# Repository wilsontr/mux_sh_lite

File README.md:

# mux_sh lite
This is a simplified version of the mux_sh accent mod board for the e-licktronic Nava TR-909 clone. It eliminates three of the sample & hold circuits attached to the multiplexer, because these circuits are unconnected to any part of the Nava accent circuitry. 

## Rationale
I had trouble getting the mux_sh boards included with my Nava to work correctly. Even after much tinkering and testing, I'd get erratic or unpredictable accent behavior from them. I'd get completely different behavior after reflowing any given solder joint on the board.  

I decided to try getting rid of the unused S&H circuits, thereby removing three opamps, several capacitors, and many traces and vias from the PCB design. So far, with the reduced density on the very small PCB, things seem to be more stable and reliable. 

[e-licktronic Nava project page](http://www.e-licktronic.com/en/nava-parts-kit/50-nava-tr909-clone.html)

[Oshpark mux_sh lite project page](https://oshpark.com/shared_projects/01qCJ78d)

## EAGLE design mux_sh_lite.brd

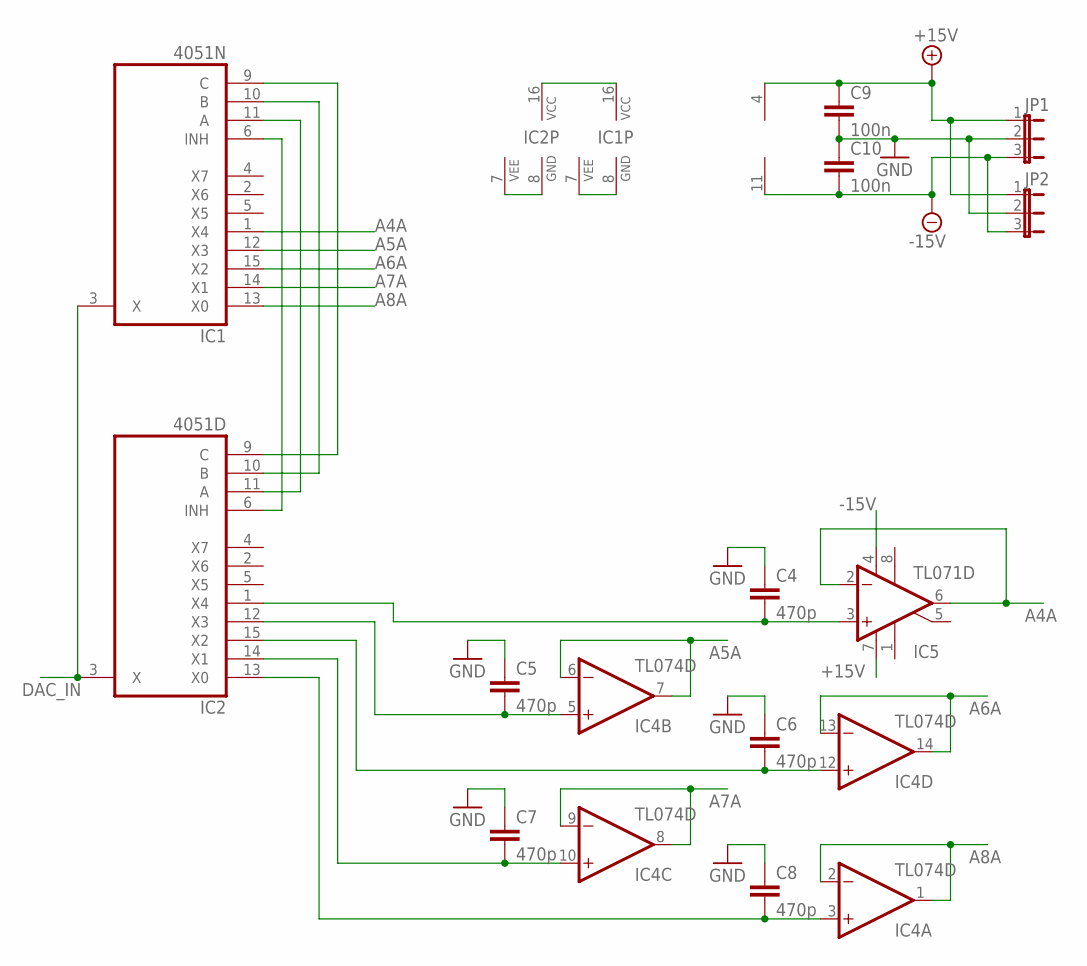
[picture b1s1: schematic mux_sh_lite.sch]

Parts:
C4, C5, C6, C7, C8: 470p; 0805
C9, C10: 100n; 0805
IC1: 4051N; DIL16
IC2: 4051D; SO16
IC4: TL074D; SO14
IC5: TL071D; SO08
JP1, JP2: JP2E; JP2

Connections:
4051_GND: IC1.7 (VEE), IC1.8 (GND)
4051_VCC: IC1.16 (VCC), IC2.16 (VCC)
+15V: C9.1, IC4.4 (V+), IC5.7 (V+), JP1.1, JP2.1
-15V: C10.2, IC4.11 (V-), IC5.4 (V-), JP1.3, JP2.3
A4A: IC1.1 (X4), IC5.2 (-IN), IC5.6 (OUT)
A5A: IC1.12 (X3), IC4.6 (-IN), IC4.7 (OUT)
A6A: IC1.15 (X2), IC4.13 (-IN), IC4.14 (OUT)
A7A: IC1.14 (X1), IC4.8 (OUT), IC4.9 (-IN)
A8A: IC1.13 (X0), IC4.1 (OUT), IC4.2 (-IN)
DAC_IN: IC1.3 (X), IC2.3 (X)
GND: C4.1, C5.1, C6.1, C7.1, C8.1, C9.2, C10.1, JP1.2, JP2.2
unnamed: IC2.7 (VEE), IC2.8 (GND)
unnamed: C5.2, IC2.12 (X3), IC4.5 (+IN)
unnamed: C4.2, IC2.1 (X4), IC5.3 (+IN)
unnamed: C6.2, IC2.15 (X2), IC4.12 (+IN)
unnamed: C7.2, IC2.14 (X1), IC4.10 (+IN)
unnamed: C8.2, IC2.13 (X0), IC4.3 (+IN)
unnamed: IC1.6 (INH), IC2.6 (INH)
unnamed: IC1.11 (A), IC2.11 (A)
unnamed: IC1.10 (B), IC2.10 (B)
unnamed: IC1.9 (C), IC2.9 (C)

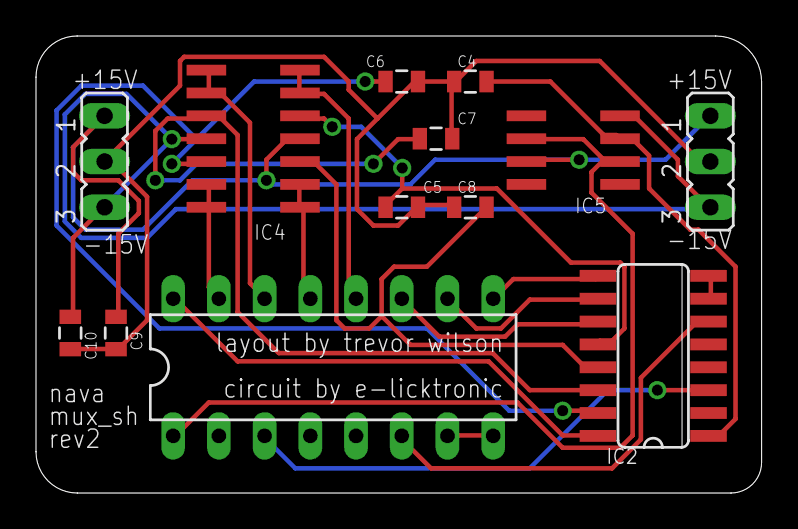
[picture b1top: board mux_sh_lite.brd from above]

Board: 2 copper layers, 40.3 x 25.4 mm, 13 parts (0 on the bottom side), 21 nets.

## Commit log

2020-03-24 Add Oshpark link

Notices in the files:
parts and their libraries:
SparkFun-Capacitors: Licensing: Creative Commons ShareAlike 4.0 International - https://creativecommons.org/licenses/by-sa/4.0
